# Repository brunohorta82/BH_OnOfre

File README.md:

# BH OnOfre
 
* [Intro](#id1)
* [Hardware](#id2)
* [Firmware](https://github.com/brunohorta82/easy_iot)
* [Video Tutoriais - YouTube](https://www.youtube.com/watch?v=OZenBfHWtak&list=PLxDLawCWayzDqAgOpIDJ-DHFAXYd_S-pr)
* [Donativos](#id6)
* [Site Oficial](http://bhonofre.pt/)

## Intro 
O projeto BH OnOfre, é uma solução IoT baseada em ESP8266 com o objetivo de tornar a automação domiciliar muito mais simples, de forma aberta e sem restrições. Todo o código fonte é aberto bem como Hardware.

**BH OnOfre Easy Light** é um dispositivo baseado em ESP8266 com 2 relés de estado sólido cada um de 2A, este permite controlar até 2 circuitos de iluminação independentes. O facto de possuir relés de estado sólido permite ligar e desligar luzes de forma silênciosa.
O OnOfre pode ser instalado atrás dos interruptores normais, possui conectores para ligar o interruptor normal, ou sensor touch. Para alem dos conectores dedicados, permite ainda ligar os mais diversos sensores/atuadores aos GPIO's disponiveis. 
O controlo do mesmo pode ser efectuado via Web, MQTT ou manualmente pelo interruptor, tem integração automatica com o Home Assistant.
Mais info em [Easy Light REPO](https://github.com/brunohorta82/BH_OnOfre/tree/master/OnOfre%20EasyLight)

## Bibliotecas necessárias 

Nome | Link | Versão 
:---: | :---: | ---:
JustWifi | [GIT](https://github.com/xoseperez/justwifi) | `last`
Timming | [GIT](https://github.com/scargill/Timing) | `last`
Async Mqtt Client | [GIT](https://github.com/marvinroger/async-mqtt-client) | `last`
ESP Async TCP | [GIT](https://github.com/me-no-dev/ESPAsyncTCP)| `last`
ESP Async Webserver | [GIT](https://github.com/me-no-dev/ESPAsyncWebServer) | `last`
Bounce2 | [GIT](https://github.com/thomasfredericks/Bounce2) | `last`
DHT Async | [GIT](https://github.com/brunohorta82/DHT_nonblocking) | `last`
Arduino Json | [ARDUINO IDE](https://arduinojson.org) | `5.*`

## Painel de Controlo 

## Hardware 
* BH OnOfre Dev Board 3.4

## Software necessário 

- Arduino Ide (caso seja para alterar o codigo fonte)
- Upload do Firmware para o ESP8266 (dentro de cada projeto o firmware está dentro da pasta binarios)
- Aceder ao AP `SSID:BH_ONFFRE_NODE_ID` e configurar a Rede Wi-Fi
- Navegar até  `http://<bh-onofre name>.local` ou `http://<bh-onofre IP address>` ou `http://192.168.4.1` ligado directamente ao módulo
- Configurar o `Wi-Fi broker`, `MQTT broker` entre outras coisas como integração automática com `Home Assistant`
- E tá feito, agora é só curtir :) 

## Caixas e Adaptadores
 - [Onofre Livolo Powered by Michaël Memeteau](https://cad.onshape.com/documents/edaf7fef18d999cab7aa6aff/w/efbde367d3f13fc563e8fda8/e/a555c81f28f9aefdf7ebc964)
 - [Onofre Protecção Eléctrica Powered by Bruno Horta](https://cad.onshape.com/documents/2658804f4fec38f38b567684/w/01661975a7b4ba3d280e6216/e/88d1bd909d651dac55006571)

## Donativos 

Se gostaste do projeto podes fazer o teu donativo :).

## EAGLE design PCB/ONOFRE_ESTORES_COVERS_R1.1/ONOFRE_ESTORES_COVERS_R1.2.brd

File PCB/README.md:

# BH OnOfre - EasyLight

* [Intro](#id1)
* [Binário](https://github.com/brunohorta82/BH_OnOfre/tree/master/OnOfre%20EasyLight/Firmware/Binario)
* [Bibliotecas necessárias](#id3)
* [Donativos](#id6)
* [Site Oficial](http://bhonofre.pt/)

## Intro 
**BH OnOfre Easy Light** é um dispositivo baseado em ESP8266 com 2 relés de estado sólido cada um de 2A, este permite controlar até 2 circuitos de iluminação independentes. O facto de possuir relés de estado sólido permite ligar e desligar luzes de forma silênciosa.
O OnOfre pode ser instalado atrás dos interruptores normais, possui conectores para ligar o interruptor normal, ou sensor touch. Para alem dos conectores dedicados, permite ainda ligar os mais diversos sensores/atuadores aos GPIO's disponiveis. 
O controlo do mesmo pode ser efectuado via Web, MQTT ou manualmente pelo interruptor, tem integração automatica com o Home Assistant.
Mais info em [Easy Light REPO](https://github.com/brunohorta82/BH_OnOfre/tree/master/OnOfre%20EasyLight)

## Bibliotecas necessárias 

Nome | Link | Versão 
:---: | :---: | ---:
JustWifi | [GIT](https://github.com/xoseperez/justwifi) | `last`
Timming | [GIT](https://github.com/scargill/Timing) | `last`
Async Mqtt Client | [GIT](https://github.com/marvinroger/async-mqtt-client) | `last`
ESP Async TCP | [GIT](https://github.com/me-no-dev/ESPAsyncTCP)| `last`
ESP Async Webserver | [GIT](https://github.com/me-no-dev/ESPAsyncWebServer) | `last`
Bounce2 | [GIT](https://github.com/thomasfredericks/Bounce2) | `last`
DHT Async | [GIT](https://github.com/brunohorta82/DHT_nonblocking) | `last`
Arduino Json | [ARDUINO IDE](https://arduinojson.org) | `5.*`

## Software necessário 

- Arduino Ide (caso seja para alterar o codigo fonte)
- Upload do Firmware para o ESP8266 (dentro de cada projeto o firmware está dentro da pasta binarios)
- Aceder ao AP `SSID:BH_ONFFRE_NODE_ID` e configurar a Rede Wi-Fi
- Navegar até  `http://<bh-onofre name>.local` ou `http://<bh-onofre IP address>`
- Configurar o `Wi-Fi broker`, `MQTT broker` entre outras coisas como integração automática com `Home Assistant`
- E tá feito, agora é só curtir :) 

## Donativos 

Se gostas-te do projeto podes fazer o teu donativo :).

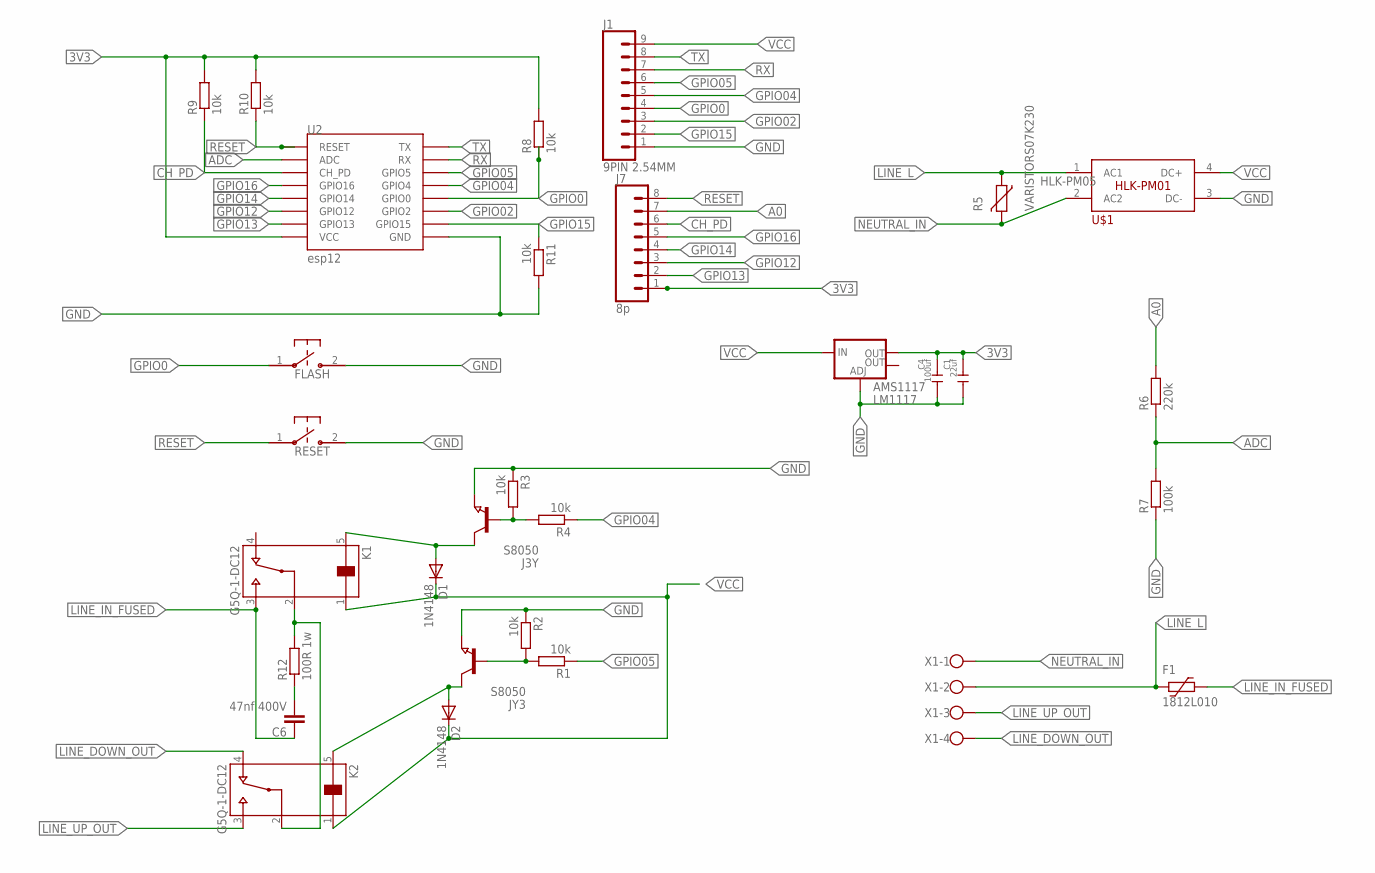
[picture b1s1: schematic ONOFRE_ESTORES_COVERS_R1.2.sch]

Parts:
AMS1117: LM1117; SOT223
C1: 22uf; C1206
C4: 100uf; C1206
C6: 47nf 400V; C102-043X133
D1, D2: 1N4148; SOD80C
F1: 1812L010; 1812L
FLASH: B3U-1000P-2P-SMD; B3U-1000P
J1: 9PIN 2.54MM; 1X09
J3Y: S8050; SOT23
J7: 8p; 1X08
JY3: S8050; SOT23
K1, K2: G5Q-1-DC12; RELAY_G5Q-1-DC12
R1, R2, R3, R4, R8, R9, R10, R11: 10k; R0603
R5: VARISTORS07K230; S07K230
R6: 220k; R0603
R7: 100k; R0603
R12: 100R 1w; R2512
RESET: B3U-1000P-2P-SMD; B3U-1000P
U2: esp12; ESP12-SMD
U$1: HLK-PM01
X1: W237-4

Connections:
3V3: AMS1117.2 (OUT), C1.1, C4.1, J7.1, R8.2, R9.2, R10.2, U2.VCC
A0: J7.7, R6.2
ADC: R6.1, R7.2, U2.ADC
CH_PD: J7.6, R9.1, U2.CH_PD
GND: AMS1117.1 (ADJ), C1.2, C4.2, FLASH.2, J1.1, J3Y.2 (E), JY3.2 (E), R2.1, R3.1, R7.1, R11.2, RESET.2, U2.GND, U$1.3 (DC-)
GPIO0: FLASH.1, J1.4, R8.1, U2.GPIO0
GPIO02: J1.3, U2.GPIO2
GPIO04: J1.5, R4.1, U2.GPIO4
GPIO05: J1.6, R1.1, U2.GPIO5
GPIO12: J7.3, U2.GPIO12
GPIO13: J7.2, U2.GPIO13
GPIO14: J7.4, U2.GPIO14
GPIO15: J1.2, R11.1, U2.GPIO15
GPIO16: J7.5, U2.GPIO16
LINE_DOWN_OUT: K2.4, X1.4
LINE_IN_FUSED: C6.1, F1.1, K1.3
LINE_L: F1.2, R5.1, U$1.1 (AC1), X1.2
LINE_UP_OUT: K2.3, X1.3
unnamed: D1.A, J3Y.3 (C), K1.5
unnamed: K1.2, K2.2, R12.2
unnamed: C6.2, R12.1
unnamed: J3Y.1 (B), R3.2, R4.2
unnamed: D2.A, JY3.3 (C), K2.5
unnamed: JY3.1 (B), R1.2, R2.2
NEUTRAL_IN: R5.2, U$1.2 (AC2), X1.1
RESET: J7.8, R10.1, RESET.1, U2.RESET
RX: J1.7, U2.RXD0 (RX)
TX: J1.8, U2.TXD0 (TX)
VCC: AMS1117.3 (IN), D1.C, D2.C, J1.9, K1.1, K2.1, U$1.4 (DC+)

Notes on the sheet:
HLK-PM05

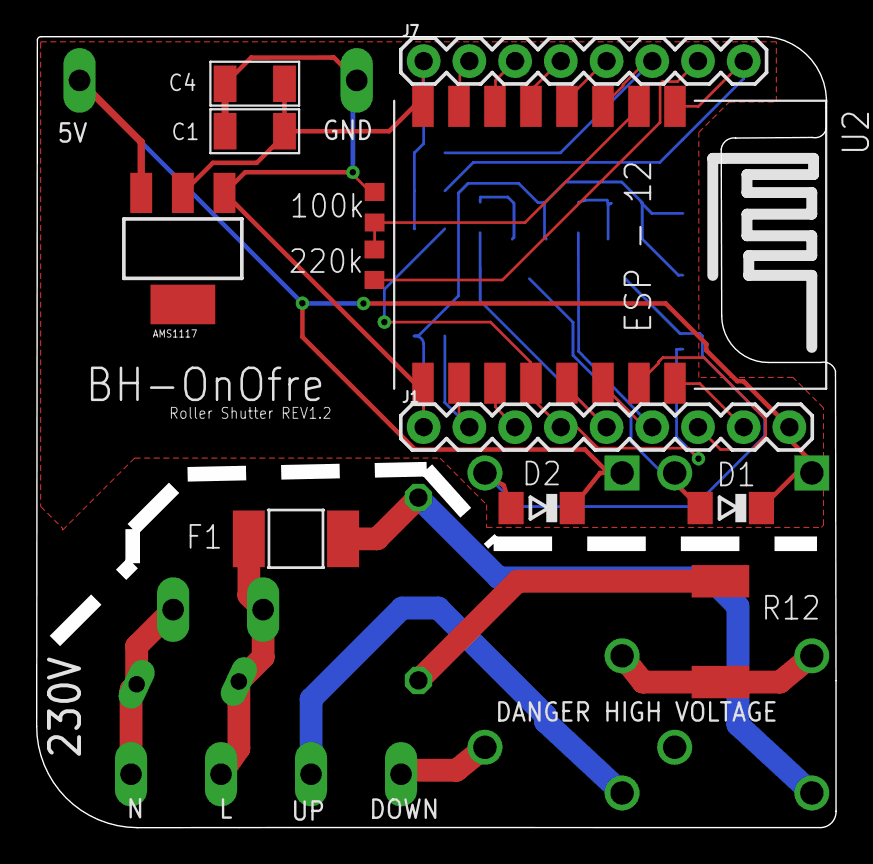
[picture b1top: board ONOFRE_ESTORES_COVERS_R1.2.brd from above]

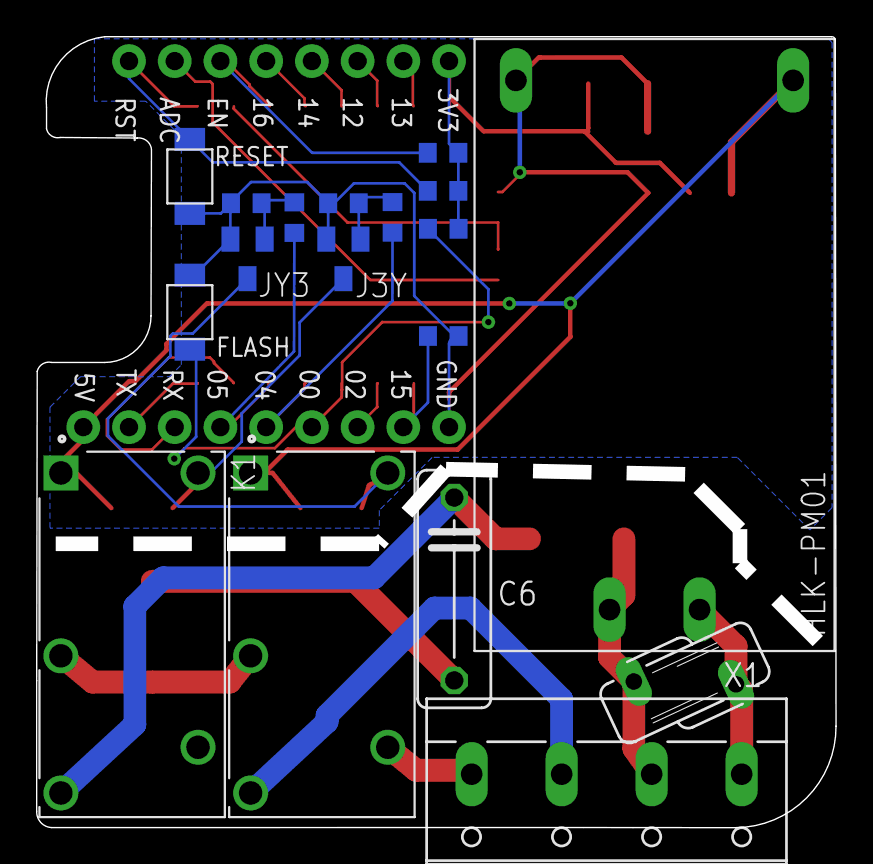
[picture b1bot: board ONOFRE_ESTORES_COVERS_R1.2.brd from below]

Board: 2 copper layers, 43.7 x 43.2 mm, 30 parts (18 on the bottom side), 29 nets.

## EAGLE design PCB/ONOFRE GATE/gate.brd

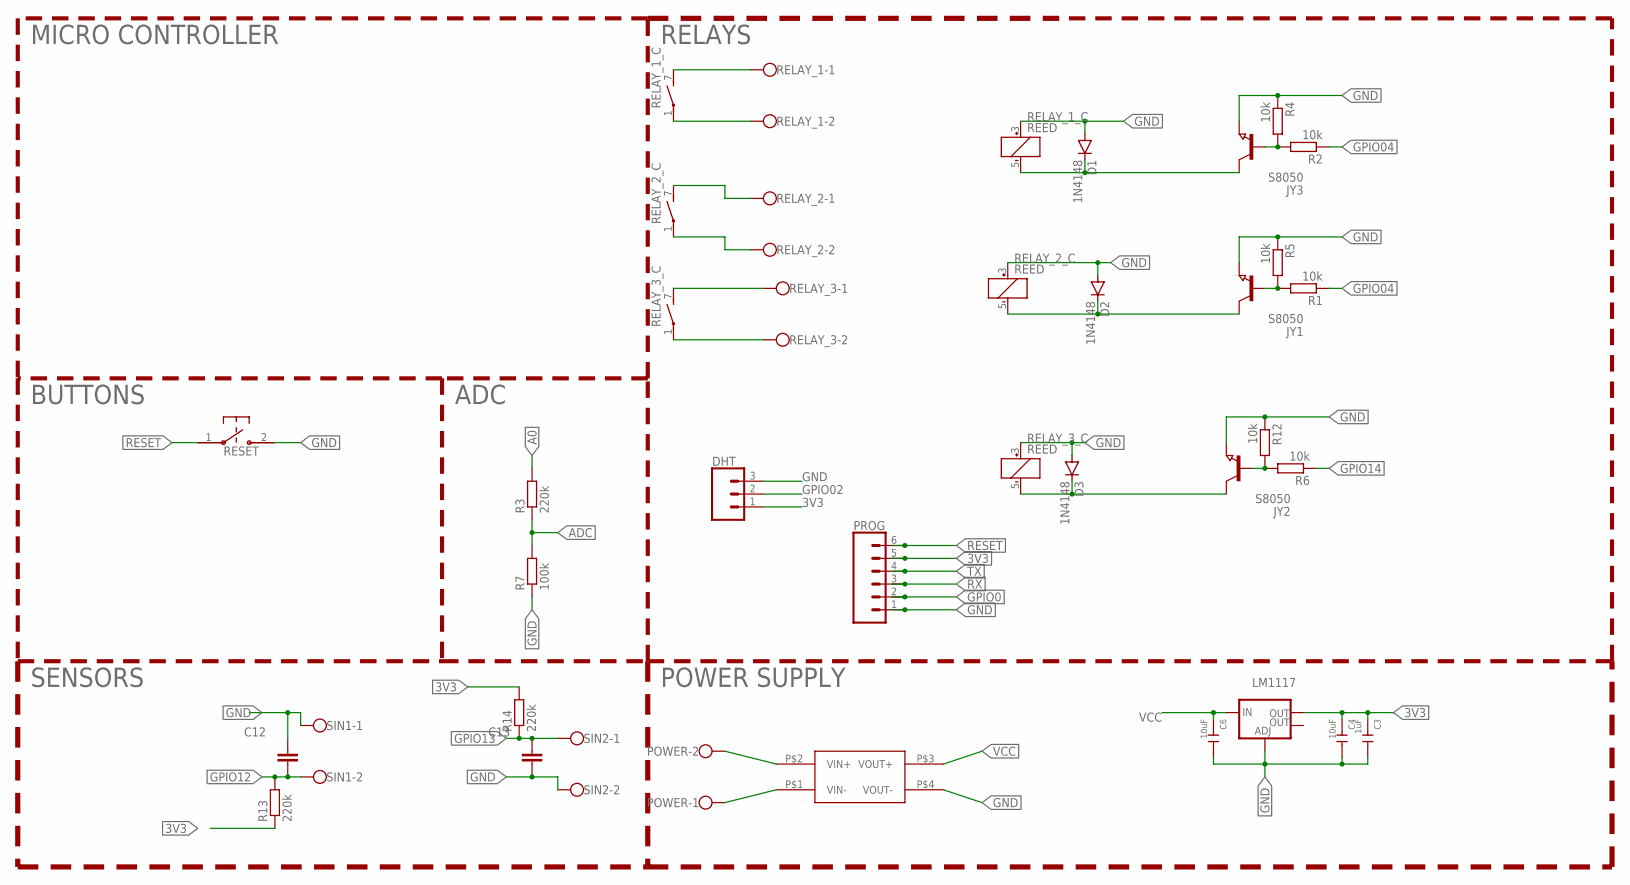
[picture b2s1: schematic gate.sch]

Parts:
AMS1117: LM1117; SOT223
C3: 1uF; C1206
C4, C6: 10uF; C1206
C12, C13: C-EUC0805; C0805
D1, D2, D3: 1N4148; SOD80C
DHT: CONN_03; 1X03
JY1, JY2, JY3: S8050; SOT23
POWER: W237-102
PROG: CONN_06NO_SILK_NO_POP; 1X06_NO_SILK
R1, R2, R4, R5, R6, R12: 10k; R0603
R3, R13, R14: 220k; R0603
R7: 100k; R0603
RELAY_1, RELAY_2, RELAY_3: W237-102
RELAY_1_C, RELAY_2_C, RELAY_3_C: REED
RESET: B3U-1000P-2P-SMD; B3U-1000P
SIN1, SIN2: W237-102
U$2: MP1584-MINI-SMDDL; MINI-DC-BRICK_DL-SMD

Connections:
3V3: AMS1117.2 (OUT), C3.1, C4.1, DHT.1, PROG.5, R13.1, R14.2
A0: R3.2
ADC: R3.1, R7.2
E: D1.C, JY3.3 (C), RELAY_1_C.5 (-)
F: D3.C, JY2.3 (C), RELAY_3_C.5 (-)
GND: AMS1117.1 (ADJ), C3.2, C4.2, C6.2, C12.1, C13.2, D1.A, D2.A, D3.A, DHT.3, JY1.2 (E), JY2.2 (E), JY3.2 (E), POWER.1, PROG.1, R4.1, R5.1, R7.1, R12.1, RELAY_1_C.3 (+), RELAY_2_C.3 (+), RELAY_3_C.3 (+), RESET.2, SIN1.1, SIN2.2, U$2.P$1 (VIN-), U$2.P$4 (VOUT-)
GND1: RELAY_1.1, RELAY_1_C.7 (S)
GND2: RELAY_2.1, RELAY_2_C.7 (S)
GND3: RELAY_3.1, RELAY_3_C.7 (S)
GPIO0: PROG.2
GPIO02: DHT.2
GPIO04: R1.1, R2.1
GPIO12: C12.2, R13.2, SIN1.2
GPIO13: C13.1, R14.1, SIN2.1
GPIO14: R6.1
unnamed: RELAY_1.2, RELAY_1_C.1
unnamed: RELAY_2.2, RELAY_2_C.1
unnamed: RELAY_3.2, RELAY_3_C.1
unnamed: JY1.1 (B), R1.2, R5.2
unnamed: JY2.1 (B), R6.2, R12.2
unnamed: JY3.1 (B), R2.2, R4.2
unnamed: POWER.2, U$2.P$2 (VIN+)
RESET: PROG.6, RESET.1
RX: PROG.3
T: D2.C, JY1.3 (C), RELAY_2_C.5 (-)
TX: PROG.4
VCC: AMS1117.3 (IN), C6.1, U$2.P$3 (VOUT+)

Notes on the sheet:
BUTTONS
MICRO CONTROLLER
ADC
RELAYS
POWER SUPPLY
SENSORS

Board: 2 copper layers, 35 parts (0 on the bottom side), 21 nets, no tracks yet.

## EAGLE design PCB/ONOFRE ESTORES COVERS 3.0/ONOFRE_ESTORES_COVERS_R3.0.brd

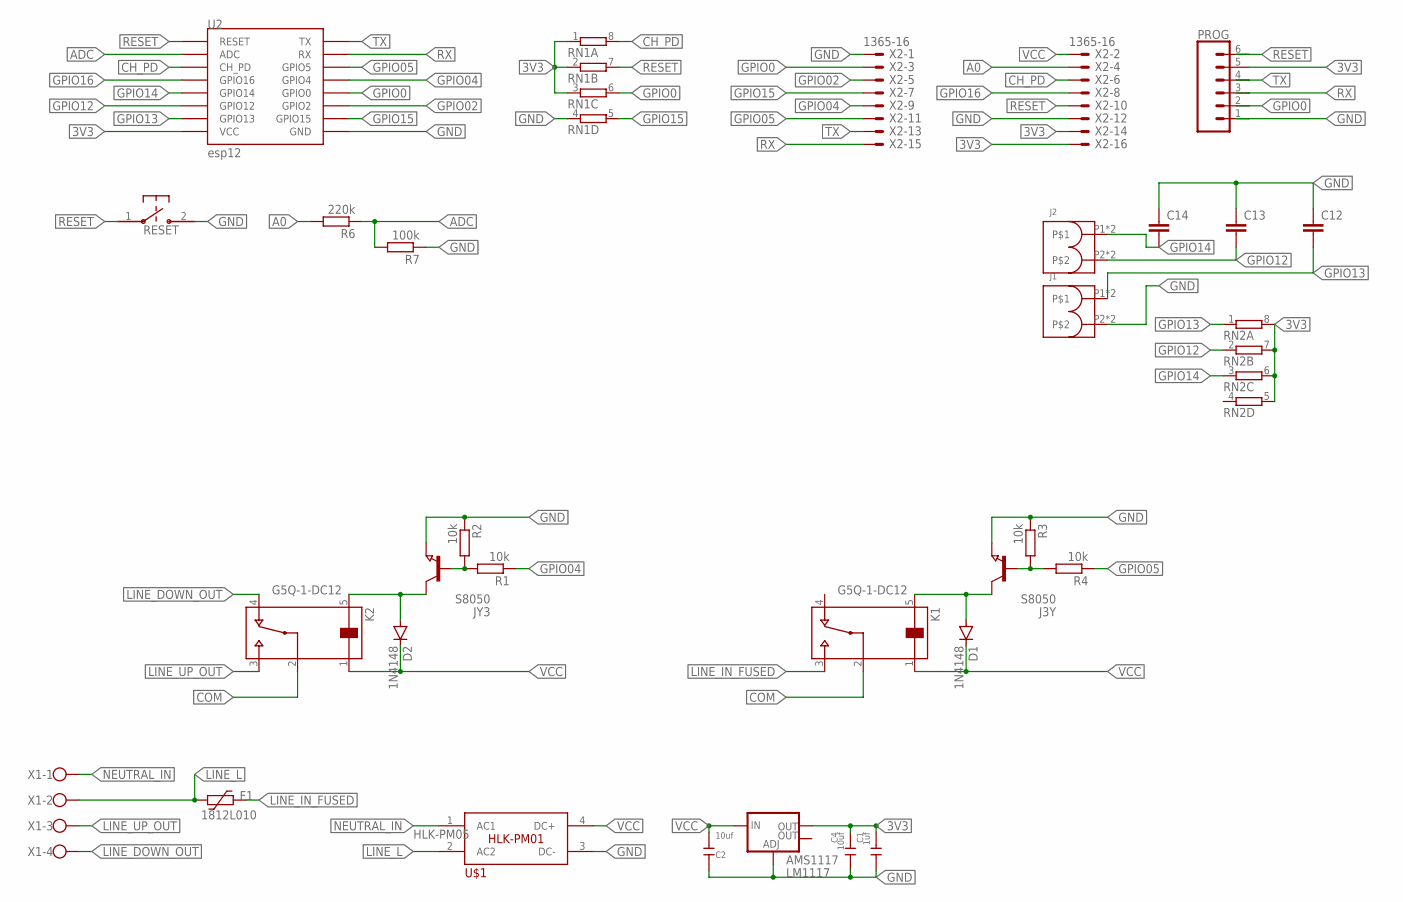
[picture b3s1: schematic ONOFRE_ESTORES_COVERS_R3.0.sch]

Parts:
AMS1117: LM1117; SOT223
C1: 1uf; C1206
C2, C4: 10uf; C1206
C12, C13, C14: C-EUC0805; C0805
D1, D2: 1N4148; SOD80C
F1: 1812L010; 1812L
J1, J2: 46.142.1001; P_46.142.1001
J3Y: S8050; SOT23
JY3: S8050; SOT23
K1, K2: G5Q-1-DC12; RELAY_G5Q-1-DC12
PROG: CONN_06NO_SILK_NO_POP; 1X06_NO_SILK
R1, R2, R3, R4: 10k; R0603
R6: 220k; R0603
R7: 100k; R0603
RESET: B3U-1000P-2P-SMD; B3U-1000P
RN1, RN2: 4R-N0603-ARV; 0603-ARV
U2: esp12; ESP12-SMD
U$1: HLK-PM01
X1: W237-4
X2: 1365-16

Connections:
3V3: AMS1117.2 (OUT), C1.1, C4.1, PROG.5, RN1.1, RN1.2 (1), RN1.3 (1), RN2.5 (2), RN2.6 (2), RN2.7 (2), RN2.8 (2), U2.VCC, X2.14, X2.16
A0: R6.2, X2.4
ADC: R6.1, R7.2, U2.ADC
CH_PD: RN1.8 (2), U2.CH_PD, X2.6
COM: K1.2, K2.2
GND: AMS1117.1 (ADJ), C1.2, C2.2, C4.2, C12.1, C13.1, C14.1, J1.P2, J1.P2.1, J3Y.2 (E), JY3.2 (E), PROG.1, R2.1, R3.1, R7.1, RESET.2, RN1.4 (1), U2.GND, U$1.3 (DC-), X2.1, X2.12
GPIO0: PROG.2, RN1.6 (2), U2.GPIO0, X2.3
GPIO02: U2.GPIO2, X2.5
GPIO04: R1.1, U2.GPIO4, X2.9
GPIO05: R4.1, U2.GPIO5, X2.11
GPIO12: C13.2, J2.P2, J2.P2.1, RN2.2 (1), U2.GPIO12
GPIO13: C12.2, J1.P1, J1.P1.1, RN2.1, U2.GPIO13
GPIO14: C14.2, J2.P1, J2.P1.1, RN2.3 (1), U2.GPIO14
GPIO15: RN1.5 (2), U2.GPIO15, X2.7
GPIO16: U2.GPIO16, X2.8
LINE_DOWN_OUT: K2.4, X1.4
LINE_IN_FUSED: F1.1, K1.3
LINE_L: F1.2, U$1.2 (AC2), X1.2
LINE_UP_OUT: K2.3, X1.3
unnamed: D1.A, J3Y.3 (C), K1.5
unnamed: J3Y.1 (B), R3.2, R4.2
unnamed: D2.A, JY3.3 (C), K2.5
unnamed: JY3.1 (B), R1.2, R2.2
NEUTRAL_IN: U$1.1 (AC1), X1.1
RESET: PROG.6, RESET.1, RN1.7 (2), U2.RESET, X2.10
RX: PROG.3, U2.RXD0 (RX), X2.15
TX: PROG.4, U2.TXD0 (TX), X2.13
VCC: AMS1117.3 (IN), C2.1, D1.C, D2.C, K1.1, K2.1, U$1.4 (DC+), X2.2

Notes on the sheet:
HLK-PM05

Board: 2 copper layers, 31 parts (6 on the bottom side), 28 nets, no tracks yet.

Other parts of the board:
U$2: DANGE_HIGH_VOLTAGE_MEDIUM

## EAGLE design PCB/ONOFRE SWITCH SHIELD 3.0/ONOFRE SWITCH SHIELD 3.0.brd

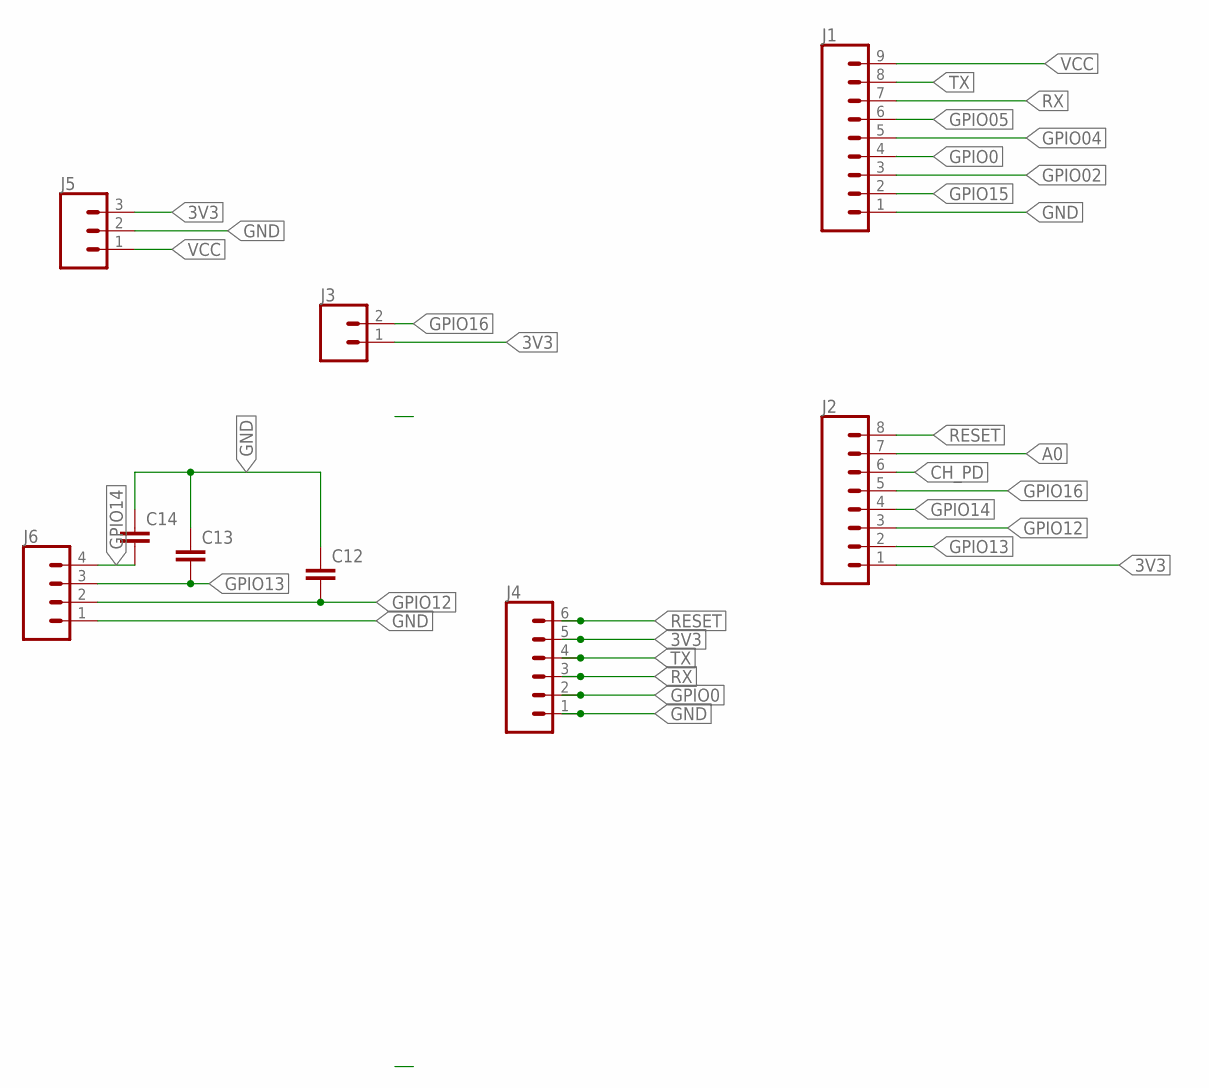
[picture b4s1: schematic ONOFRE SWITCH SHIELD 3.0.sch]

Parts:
C12, C13, C14: C-EUC0805; C0805
J1: CONN_09; 1X09
J2: CONN_08"; 1X08
J3: CONN_02; 1X02
J4: CONN_06NO_SILK_NO_POP; 1X06_NO_SILK
J5: CONN_03; 1X03
J6: CONN_04; 1X04

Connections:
3V3: J2.1, J3.1, J4.5, J5.3
A0: J2.7
CH_PD: J2.6
GND: C12.1, C13.1, C14.1, J1.1, J4.1, J5.2, J6.1
GPIO0: J1.4, J4.2
GPIO02: J1.3
GPIO04: J1.5
GPIO05: J1.6
GPIO12: C12.2, J2.3, J6.2
GPIO13: C13.2, J2.2, J6.3
GPIO14: C14.2, J2.4, J6.4
GPIO15: J1.2
GPIO16: J2.5, J3.2
RESET: J2.8, J4.6
RX: J1.7, J4.3
TX: J1.8, J4.4
VCC: J1.9, J5.1

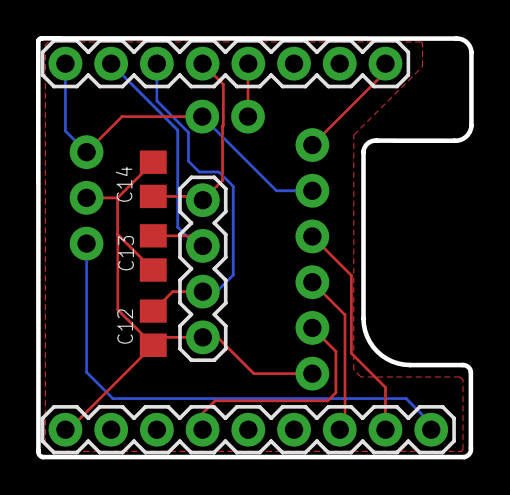
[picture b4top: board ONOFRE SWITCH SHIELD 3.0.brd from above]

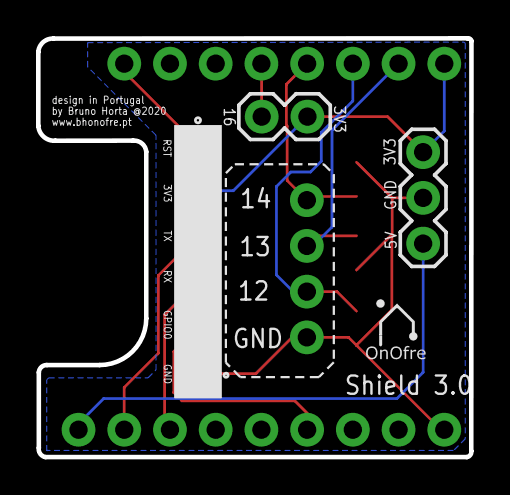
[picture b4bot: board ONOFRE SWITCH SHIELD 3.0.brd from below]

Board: 2 copper layers, 24.1 x 23.3 mm, 9 parts (2 on the bottom side), 11 nets.

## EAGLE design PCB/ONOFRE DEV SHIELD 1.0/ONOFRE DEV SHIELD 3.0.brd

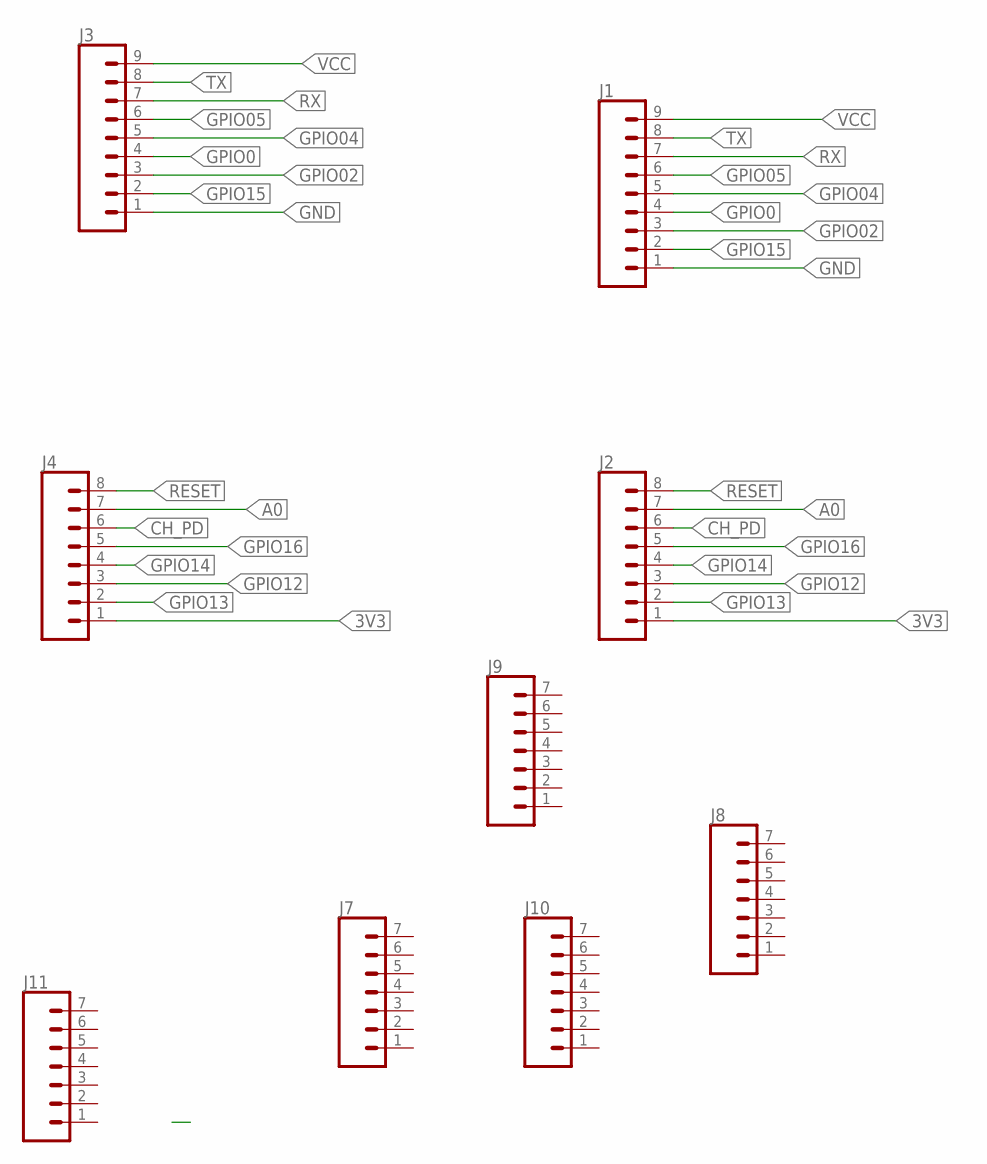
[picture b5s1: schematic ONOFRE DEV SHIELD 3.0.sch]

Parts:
J1, J3: CONN_09; 1X09
J2, J4: CONN_08"; 1X08
J7, J8, J9, J10, J11: CONN_07NO_SILK; 1X07_NO_SILK

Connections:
3V3: J2.1, J4.1
A0: J2.7, J4.7
CH_PD: J2.6, J4.6
GND: J1.1, J3.1
GPIO0: J1.4, J3.4
GPIO02: J1.3, J3.3
GPIO04: J1.5, J3.5
GPIO05: J1.6, J3.6
GPIO12: J2.3, J4.3
GPIO13: J2.2, J4.2
GPIO14: J2.4, J4.4
GPIO15: J1.2, J3.2
GPIO16: J2.5, J4.5
RESET: J2.8, J4.8
RX: J1.7, J3.7
TX: J1.8, J3.8
VCC: J1.9, J3.9

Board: 2 copper layers, 9 parts (2 on the bottom side), 17 nets, no tracks yet.

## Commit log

2017-12-01 no message
2017-12-25 Organização de ficheiros e versões do OnOfre, devenvolvimento da dev board
2017-12-25 Header pins para ligar os relés
2017-12-25 melhoramentos nas pistas da dev board
2017-12-26 ficheiros para fazer a PCB na CNC
2017-12-29 problema de pull up dos relés resolvido, alteração da fonte de 3.3v para 5v
2018-01-05 nova board
2018-01-07 Versão Square em DEV
2018-01-11 fix relay position
2018-01-11 organização de PCB testadas , não testadas e em desenvolvimento
2018-01-12 OnOfre Square rev2 80% pronto
2018-01-13 Square Rev2 pronto para testes
2018-01-15 versão 3 com sensor de corrente, permite medir consumos
2018-01-16 REV1 teste OK demo em https://youtu.be/ygMf2j0tS-s
2018-01-20 change switch place
2018-01-20 fix labels, gerber files
2018-02-17 Organização do repositorio
2018-03-05 Rev3.1 dual
2018-03-05 Lista de Componentes
2018-03-16 Firmware para 2 touchs
2018-03-21 3.2 Via por baixo do ESP8266 mudada de sitio
2018-04-02 OnOnfre_dual_mola_ssr_rev3.2
2018-04-03 Otimização do Firmware do BH OnOfre ESP12
2018-04-03 resolvido a troca na label dos pinos 04 e 05
2018-04-06 código para interruptores mecanicos
2018-04-07 novos firmwares, firmware para estores com interruptor manual
2018-04-07 Novos firmwares, estores
2018-04-10 Código para implementar no OnOfre Slave para vão de escada
2018-04-11 Rev 3.4, alteração de labels e numero de pinos
2018-04-19 nova versão OnOfre Parafuso com 2 relés de estado sólido
2018-04-27 estores e tomada em progresso
2018-05-05 Novo Firmware
2018-05-07 Firmware para estores, com integração auto no homeassistant e update de firmware via OTA e via Browser
2018-05-07 Firmware para 2 switch com Ota e browser update
2018-05-07 Firmware para pulsar durante meio segundo, ex: liga o relé e passado meio segundo desliga
2018-05-09 Labels Fix
2018-05-22 remoção do OTA Arduino e adição de OTA via Web
2018-06-21 pdf com esquema
2018-07-03 retain nos componentes do Home assistant
2018-07-14 Rev3.5 Parafuso
2018-08-31 Alteração de Nomes de Boards
2018-08-31 Organização de Boards
2018-08-31 organização de pastas
2018-08-31 html
2018-08-31 webswitch
2018-09-14 Nova plataforma de gestao de switchs
2018-09-20 versão beta 1
2018-09-20 update read me
2018-09-21 easy light board
2018-09-21 gerber
2018-09-21 versão 1.1 correcção do auto redirecionamento quando mudamos o nome do nó
2018-09-23 VERSION 1.2
2018-09-23 Binário V1.2 EASY LIGHT
2018-09-23 correcção de erros nos textos
2018-09-24 Versão 1.3, suporte para DHT11, DHT21 e DHT22
2018-10-01 versão 1.5
    Correcção do BUG no topico dos sensores de temperatura.
    Adição de suporte e migração entre diferentes versões de firmware
2018-10-01 binário v1.5
2018-10-02 Bug Fix
    nao desliga o AP depois de configurado o Wi-FI - Resolvido
    remoção do "a" perdido
    update da config apos alteração do nome do NÓ
    update do mDNS apois alteraçao do nome do NÓ
2018-10-02 BH_OnOfre_Easy_Light_v1.51.bin
2018-10-02 chain requests
2018-10-09 configuração de IP estatico, configuração de password no AP
2018-10-09 atualização do painel de controlo
2018-10-09 suporte para Dallas Sensors
2018-10-09 alteração do nome da funçao do sensor
2018-10-11 V1.60 Suporte para DS18B20, configuração de IP Fixo, Configuração de Nome de funcionalidade de cada sensor, ex temperatura
2018-10-11 Mapeamento de GPIOS em Uso
2018-10-11 v1.6
2018-10-12 Easy blinds Firmware Beta
2018-10-12 Easyblinds
2018-10-14 Correcção de BUG na edição do Nome da função do sensor Humidade
2018-10-14 estores controlo via painel de controlo
2018-10-14 estores push ready
    estores push ready
2018-10-16 disponibilização dos GPIO's 16 e 14 nos switch e implementação de PULLDOWN_16
2018-10-17 Possibilidade de usar outros GPIOs no switch (14-16)
2018-10-18 V.162
2018-10-21 board
    board
2018-10-23 rev4.0
2018-10-23 rev5.0dev
2018-11-01 Revert "rev5.0dev"
    This reverts commit 2e2358a8c57761c3fa030a0a65c911856fe9a90b.
2018-11-01 Revert "Revert "rev5.0dev""
    This reverts commit b527e27402ec8f63df68f9227db4901d182b5901.
2018-11-04 junção do codigo do BHPZEM com o do BH OnOfre
    Criação de codigo uniforme para todos os devices BH ou devices baseados em ESP8266 -> BH EASY IOT
2018-11-08 adicionar e remover novos switchs
2018-11-10 fix switch
2018-11-10 Firmware 2.1
    Possibilidade de adicionar mais Swichs Fisicos ou virtuais
    Possibilidade de adicionar mais relés
    BUG FIX - Perda dos Swiths gravados
    BUG FIX - Memoria de estado invalido com o MQTT
2018-11-10 Binário 2.1
2018-11-10 updaye readme
2018-11-12 correcção de bug ao adicionar relés
2018-11-12 Versão 2.4
2018-11-12 Novos binários versão 2.4
2018-11-12 BH ONOFRE
2018-11-13 open close switch
2018-11-13 Easy Config
2018-11-14 versão 2.5
    Configuração Facil para Estores ou Interruptor duplo
2018-11-14 versão 2.6 Estores via MQTT
2018-11-14 Versão 2.7 resolução do bug na publicação de estado dos estores via MQTT
2018-11-15 correcção do bug de State Position na integração do home assistant com o tipo Cover
2018-11-15 Versão 2.9 BUG FIX: correcção de Abertura ou Fecho de estore caso o sistema reinicie
2018-11-16 Passagem do Firmware para novo Repo https://github.com/brunohorta82/BH-Easy-Iot
2018-11-16 caixas e adaptadores
2018-11-16 docs
2018-11-16 rev 5 in progress
2018-12-13 beta2 board 5A
2018-12-14 REV5
    REV5 IN PROGRESS
2018-12-14 rev5
2018-12-14 rev 5
2018-12-17 rev5 adc A0
2018-12-18 rev1.0 single
2018-12-20 pcb single
2019-01-10 rev5.1
    remoção de diodos e slot para relés mecanicos
2019-01-10 Revert "rev5.1"
    This reverts commit eb04db9ecb2416f00214f08c4929ad914bbcba1f.
2019-01-10 Revert "sol"
    This reverts commit 5e2c5b42127c6a8382e434407ba92e7f1eb271ca.
2019-01-18 Caixas Rev5
2019-01-18 board
2019-04-05 snub
2019-04-06 estores
2019-04-18 shield wire
2019-05-08 estores rev1
2019-05-28 shield fix
2019-06-06 REMOÇÃO DE PCB'S ANTIGAS E BETAS
2019-06-07 ADD MADE IN PORTUGAL LABEL
2019-06-07 ADD NEW SLOT OVER N AND L
2019-07-07 rename folder
2019-07-07 Rename Folders, Alteração de nome de pastas
    Rename folders to support EN and PT
    Alteração de nome de pastas para EN e PT
2019-07-20 shield v2
2019-08-27 update values Onofre Cover V1
2020-01-11 Onofre Shields Dev and REV3
2021-02-25 new boards
2021-02-25 1.2 legacy cover

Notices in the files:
parts and their libraries:
SparkFun-Connectors: Licensing: Creative Commons ShareAlike 4.0 International - https://creativecommons.org/licenses/by-sa/4.0
